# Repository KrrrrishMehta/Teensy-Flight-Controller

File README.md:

# Agastya V1.0 - Quadcopter Flight Controller

Welcome to the repository for the **Agastya V1.0**, a custom-built quadcopter flight controller project by Team Phoenix. This project includes the complete firmware and details about the custom-designed Printed Circuit Board (PCB).

---

## 📋 Table of Contents

- [Overview](#-overview)
- [Hardware](#-hardware)
  - [Custom PCB: Agastya V1.0](#custom-pcb-agastya-v10)
  - [Components](#components)
- [Software & Firmware](#-software--firmware)
  - [Key Features](#key-features)
  - [Control System](#control-system)
- [Getting Started](#-getting-started)
  - [Prerequisites](#prerequisites)
  - [Setup & Flashing](#setup--flashing)
- [Flight & Tuning](#-flight--tuning)
  - [Pre-flight Checklist](#pre-flight-checklist)
  - [PID Tuning](#pid-tuning)
- [Contributing](#-contributing)

---

## 🚁 Overview

This project is a complete flight controller solution for a quadcopter. The firmware is written in C++ for the Arduino environment and is designed to run on a custom PCB, the "Agastya V1.0". The system reads data from an Inertial Measurement Unit (IMU), processes it through a Kalman filter, takes commands from an RC receiver, and uses a PID control loop to stabilize the drone and control its flight.

---

## 🔩 Hardware

### Custom PCB: Agastya V1.0

The heart of this project is a custom-designed PCB that integrates all the necessary components for a clean and reliable build.

[]
*Assembly diagram for the Agastya V1.0 flight controller board.*

*PCB Assembly for the Agastya V1.0 flight controller board.*

### Components

- **Microcontroller:** An Arduino-compatible microcontroller (e.g., Teensy, Arduino Nano/Pro Mini).
- **IMU:** MPU-6050 Gyroscope & Accelerometer.
- **RC Receiver:** A receiver that outputs a PPM (Pulse Position Modulation) signal.
- **ESCs:** Four Electronic Speed Controllers for brushless motors.
- **Optional:** A barometer for altitude hold and a display for telemetry (connections are available on the PCB).

---

## 💻 Software & Firmware

The firmware is designed to be robust, efficient, and tunable. It's built on standard Arduino libraries for broad compatibility.

### Key Features

- **Sensor Fusion:** A 1D Kalman Filter is implemented to fuse noisy accelerometer data with drifty gyroscope data, providing a stable angle estimate for roll and pitch.
- **Gyro Calibration:** An automatic gyroscope calibration sequence runs at startup to cancel out sensor bias, ensuring stable flight.
- **PPM Receiver Support:** Reads up to 8 channels from a PPM RC receiver.
- **Fixed-Time Loop:** The main control loop runs at a consistent **250Hz (4ms)**, which is critical for stable PID performance.
- **Safety Features:**
  - **Arming Check:** The drone will not arm until a specific switch is activated on the transmitter.
  - **Throttle Cut-off:** When the throttle stick is at its lowest position, the motors are stopped, and the PID controllers are reset to prevent integral windup.

### Control System

The flight controller uses a cascaded PID control system. The current code is configured for **Rate (Acro) Mode**.

1.  **Rate PID Controller:** This is the inner loop that controls the drone's angular velocity (how fast it rotates). It takes the desired rotation rate from the pilot's sticks and works to match the drone's actual rotation rate (from the gyro) to that target.
2.  **Angle PID Controller (Level Mode):** *This loop is present in the code but is currently commented out.* When enabled, it forms the outer loop. It takes a desired angle from the pilot's sticks and calculates the necessary rotation rate to achieve that angle. This rate is then fed into the Rate PID controller.

---

## 🚀 Getting Started

### Prerequisites

1.  [Arduino IDE](https://www.arduino.cc/en/software)
2.  Required Libraries:
    - `<Wire.h>` (usually included with Arduino IDE)
    - `<Servo.h>` (usually included with Arduino IDE)
    - `<PulsePosition.h>` (Install via the Arduino Library Manager)
3.  Assembled Agastya V1.0 PCB or a breadboard equivalent.

### Setup & Flashing

1.  **Clone the Repository:**
    ```bash
    git clone [your-repository-url]
    ```
2.  **Open in Arduino IDE:** Open the `.ino` file in the Arduino IDE.
3.  **Select Board & Port:** Go to `Tools > Board` and select the microcontroller you are using. Then, select the correct COM port under `Tools > Port`.
4.  **Upload:** Click the "Upload" button to flash the firmware to the board.

---

## 🛠️ Flight & Tuning

**⚠️ WARNING: Always remove propellers before testing, calibrating, or flashing the flight controller.**

### Pre-flight Checklist

1.  Ensure the battery is fully charged.
2.  Place the drone on a perfectly level surface before powering on to ensure correct gyro calibration.
3.  Power on your transmitter first, then the drone.
4.  Check that the arming switch works as expected. The motors should not spin until armed.
5.  Perform a quick control check (without props) to ensure roll, pitch, and yaw respond correctly.

### PID Tuning

PID tuning is critical for stable, responsive flight. The gains are located at the top of the source code file.

```cpp
// --- RATE PID GAINS (Tuning Parameters) ---
float PRateRoll = 0.6;
float PRatePitch = PRateRoll;
float PRateYaw = 0;

float IRateRoll = 0.0;
float IRatePitch = IRateRoll;
float IRateYaw = 0;

float DRateRoll = 0.000;
float DRatePitch = DRateRoll;
float DRateYaw = 0;
```

- **P (Proportional):** This is the main gain. Increase it for a sharper, more responsive feel. If it's too high, the drone will oscillate rapidly.
- **I (Integral):** This gain corrects for drift and external forces like wind. Increase it to help the drone hold its angle. If it's too high, the drone will feel "sluggish" and may oscillate slowly.
- **D (Derivative):** This acts as a dampener. Increase it to smooth out the "kick" from the P-gain and reduce overshoot. If it's too high, the motors may get hot and you'll hear high-frequency noise.

**Tuning Process:**
1.  Start with I and D gains at zero.
2.  Increase the P-gain until you see fast oscillations, then back it off by about 20-30%.
3.  Increase the D-gain to smooth out the flight.
4.  Finally, slowly increase the I-gain to help the drone resist drift.

---

## 🤝 Contributing

Contributions are welcome! If you have improvements for the code or hardware, please feel free to fork this repository and submit a pull request.

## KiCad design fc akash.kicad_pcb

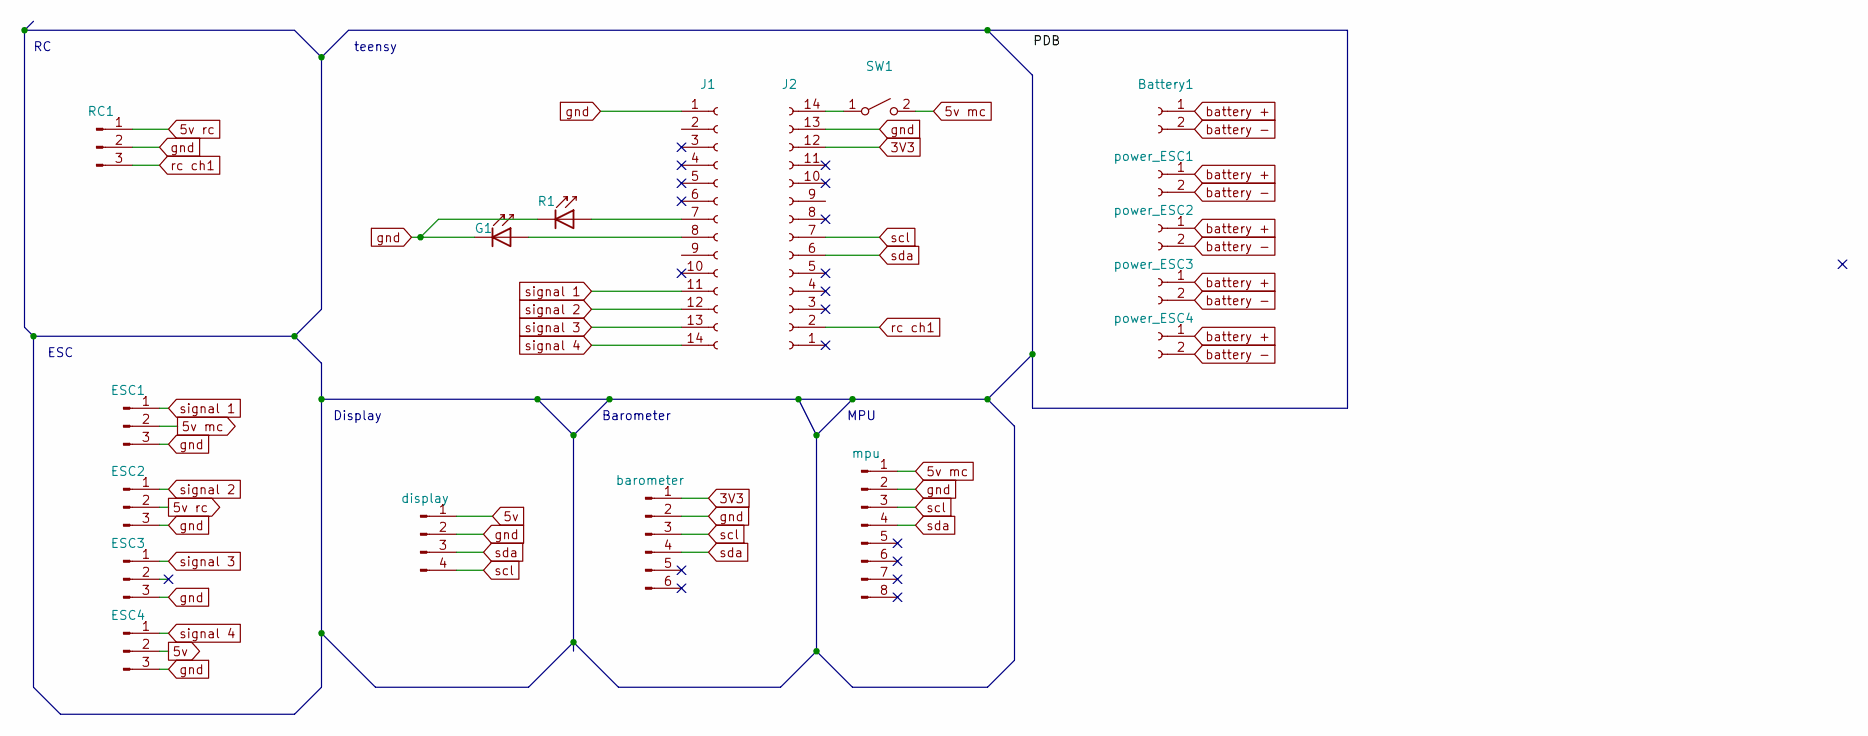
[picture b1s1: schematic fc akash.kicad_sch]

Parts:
Battery1: Conn_01x02_Socket; SolderWire-0.25sqmm_1x02_P4.5mm_D0.65mm_OD2mm
ESC1, ESC2, ESC3, ESC4: Conn_01x03_Pin; PinHeader_1x03_P2.54mm_Vertical
G1: SFH482; LED_D5.0mm_FlatTop
J1, J2: Conn_01x14_Socket; PinHeader_1x14_P2.54mm_Vertical
J3: mpu; PinHeader_1x08_P2.54mm_Vertical
J5: barometer; PinHeader_1x06_P2.54mm_Vertical
J6: display; PinHeader_1x04_P2.54mm_Vertical
R1: SFH482; LED_D5.0mm_FlatTop
RC1: Conn_01x03_Pin; PinHeader_1x03_P2.54mm_Vertical
SW1: SW_SPST; PinSocket_1x03_P2.54mm_Vertical
power_ESC1, power_ESC2, power_ESC3, power_ESC4: Conn_01x02_Socket; battery connector banana

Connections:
3V3: J2.12, J5.1
5v: ESC4.2, J6.1
5v mc: ESC1.2, J3.1, SW1.2 (B)
5v rc: ESC2.2, RC1.1
unnamed: G1.2 (A), J1.8
unnamed: J1.7, R1.2 (A)
unnamed: J2.14, SW1.1 (A)
battery +: Battery1.1, power_ESC1.1, power_ESC2.1, power_ESC3.1, power_ESC4.1
battery -: Battery1.2, power_ESC1.2, power_ESC2.2, power_ESC3.2, power_ESC4.2
gnd: ESC1.3, ESC2.3, ESC3.3, ESC4.3, G1.1 (K), J1.1, J2.13, J3.2, J5.2, J6.2, R1.1 (K), RC1.2
rc ch1: J2.2, RC1.3
scl: J2.7, J3.3, J5.3, J6.4
sda: J2.6, J3.4, J5.4, J6.3
signal 1: ESC1.1, J1.11
signal 2: ESC2.1, J1.12
signal 3: ESC3.1, J1.13
signal 4: ESC4.1, J1.14

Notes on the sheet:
ESC
MPU
teensy
Barometer
Display

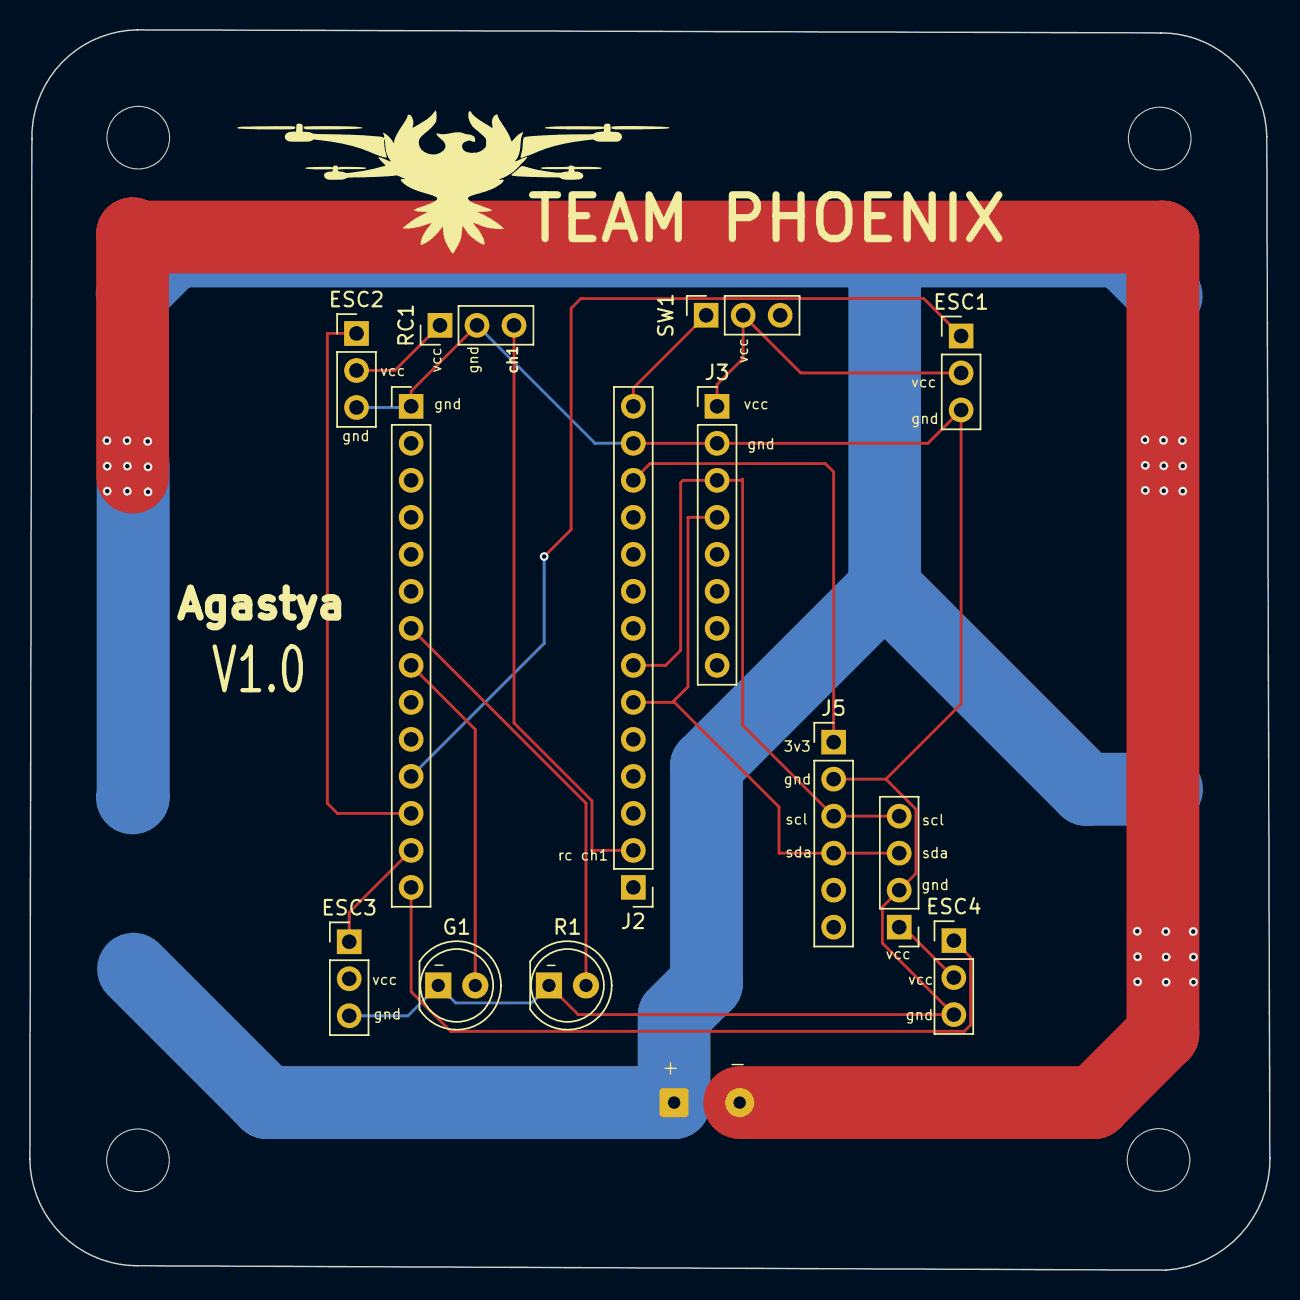
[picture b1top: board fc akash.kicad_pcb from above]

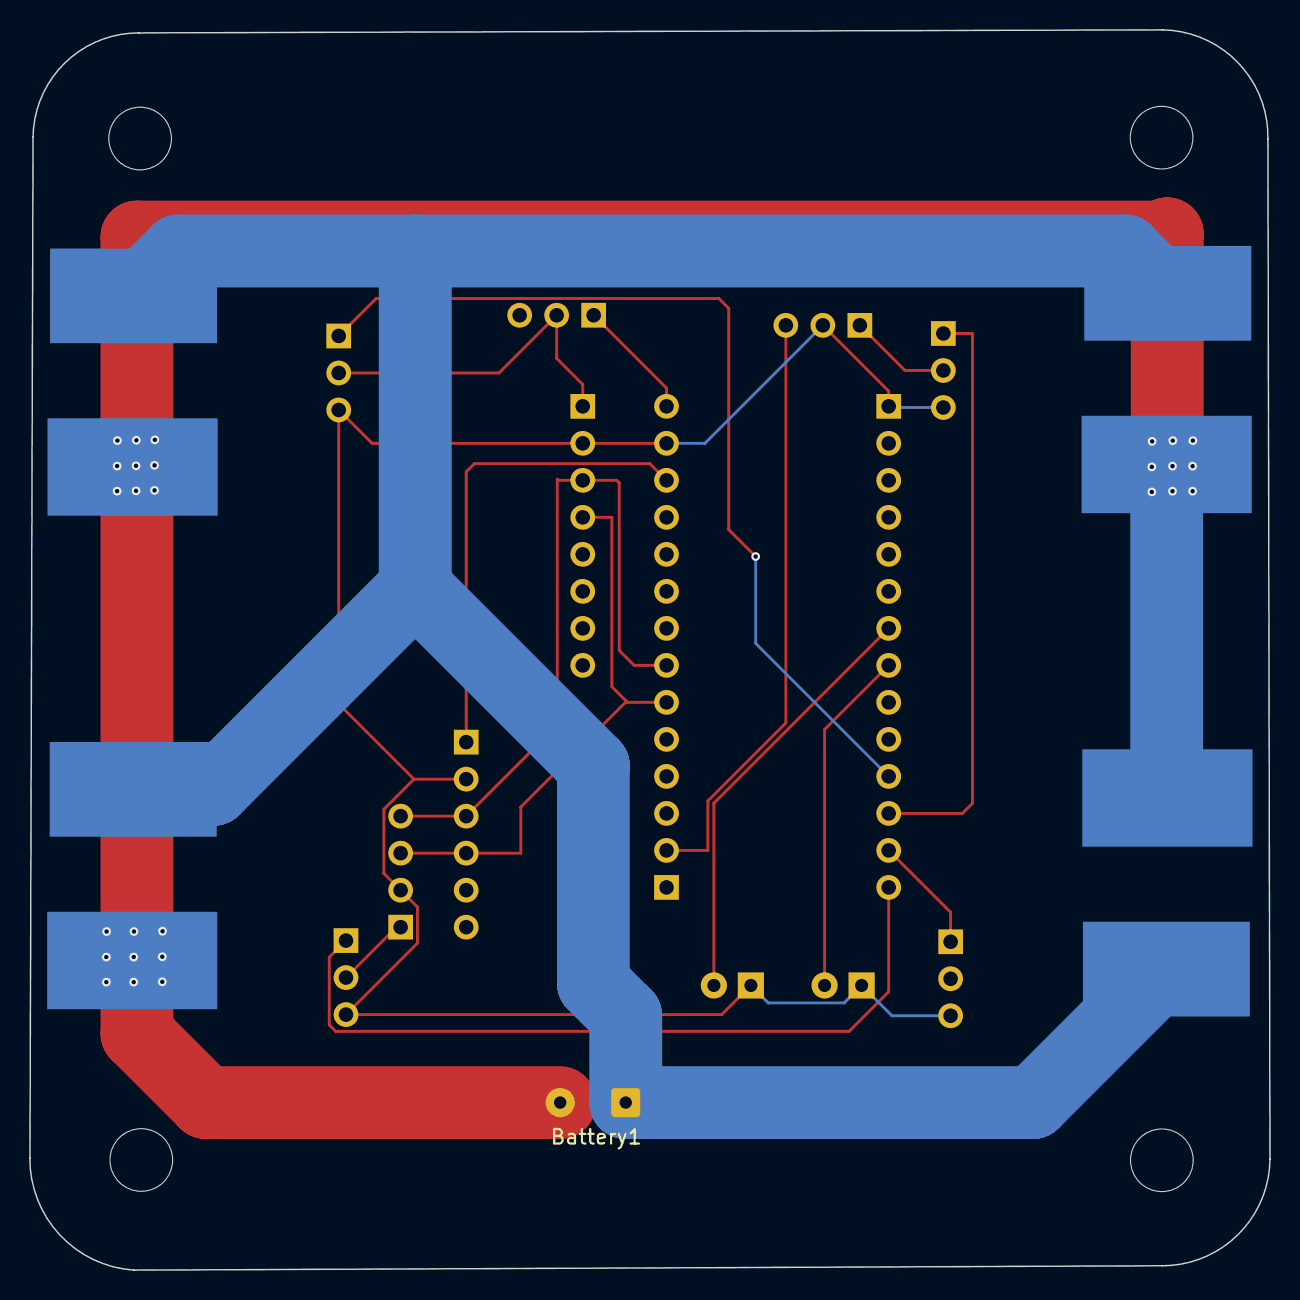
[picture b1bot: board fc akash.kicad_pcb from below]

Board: 2 copper layers, 85.1 x 85.1 mm, 18 parts (5 on the bottom side), 17 nets.

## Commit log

2025-08-14 Docunments/FC akash kikad files added
2025-08-14 README.md
